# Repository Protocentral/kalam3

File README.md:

# ProtoCentral Kalam v3 IOT platform

ProtoCentral Kalam v3 is our newest IOT platform based on the ESP8266 Wi-Fi SoC. It's easy-to-use, low cost and easily scalable. 

IoT is now made easy with quick plug-and-play functionality in both hardware and software. Based on the popular ESP8266 Wi-Fi SoC from Espressif, this board contains everything required, right out of the box.

Features
--------
* ESP8266EX WiFi System-on-Chip (SoC) with ARM Cortex M3 microcontroller
* On-board 2.4 GHz PCB antenna
* FTDI-based USB-UART interface with microUSB connector
* Fully compatible with the Arduino IDE
* Single Li-Ion battery powered
* On-board battery charger
* 31-pin Hirose DF-9 connector on the back for expansion

Repository Contents
-------------------
* **/hardware** - All Eagle design files (.brd, .sch)
* **/libraries** - Arduino libraries and example code
* **/docs** - Additional Documentation

Board Overview
--------------

Kalam Starter Kit
---------
[Kalam Starter Kit Documentation](docs/starter_kit/README.md)

Getting Started with Kalam
--------------------------

Connect the GPIO expander cap to the Kalam V3 by stacking it on top.Now that the setup is complete,the setup needs to be powered up.Attach a Li-poly battery to the Kalam v2 Iot board.Control the power using the on/off switch

How to setup Arduino support for Kalam (using Sparkfun thing Dev)
---------------------------------------------------
Kalam is powered by the Sparkfun's board support file.The first thing you will need to do is to download the latest release of the Arduino IDE. You will need to be using version 1.6.4 or higher. 
After you have downloaded and installed v1.6.4, you will need to start the IDE and navigate to the Preferences menu.
Sparkfun's  JSON url for ESP8266 board is - https://raw.githubusercontent.com/sparkfun/Arduino_Boards/master/IDE_Board_Manager/package_sparkfun_index.json

* Click Ok to close and save the preferences
* Then click Tools > Board > Board Manager
* You should find Sparkfun ESP8266 boards listed in the Board Manager window.

*	Press the “Install” button on the chosen ESP8266 category.The download process will begin
* Reboot Arduino and look under Tools > Boards and you should see the addition of the Sparkfun boards in your board list.

Getting Started with ThingSpeak
-------------------------------
The Internet of Things (IoT) provides access to a broad range of embedded devices and web services. ThingSpeak is an IoT platform that enables you to collect, store, analyze, visualize, and act on data from sensors or actuators.The primary element of ThingSpeak activity is the channel, which contains data fields, location fields, and a status field. After you create a ThingSpeak channel, you can write data to the channel, process and view the data  and react to the data.

Setup ThingSpeak
----------------
ThingSpeak requires a user account and a channel. A channel is where you send data and where ThingSpeak stores data. Each channel has up to 8 data fields, location fields, and a status field. You can send data every 15 seconds to ThingSpeak.

* Sign up for new User Account – https://thingspeak.com/users/sign_up

* Create a new Channel by selecting Channels, My Channels, and then New Channel

You can change the name to fit your need and you can add a description corresponding to the channel. You can add any other useful description into the metadata field. In the same page, you should see the fields for Latitude, Longitude and Elevation. Also, you can make the channel as "Private" or "Public".

Once you have edited the fields, click on ‘Save Channel’ button.

Setup Arduino Sketch
--------------------

We have provided a few Arduino sketch examples . They are designed to work right away with no changes.  To make the examples work with your ThingSpeak channel, you will need to configure the myChannelNumber and myWriteAPIKey variables.

  ```
const char* tokenid = "OFZEOKCL95S8HRNI"

  ```
Running a sketch
-----------------------------------
Load the example in the Arduino IDE. Make sure to select the board as "Sparkfun ESP8266 Thing Dev"  and COM port. Then, upload the code to your Kalam.

License Information
-------------------
This product is open source!

Please use, reuse, and modify these files as you see fit. Please maintain attribution to Protocentral and release anything derivative under the same license.

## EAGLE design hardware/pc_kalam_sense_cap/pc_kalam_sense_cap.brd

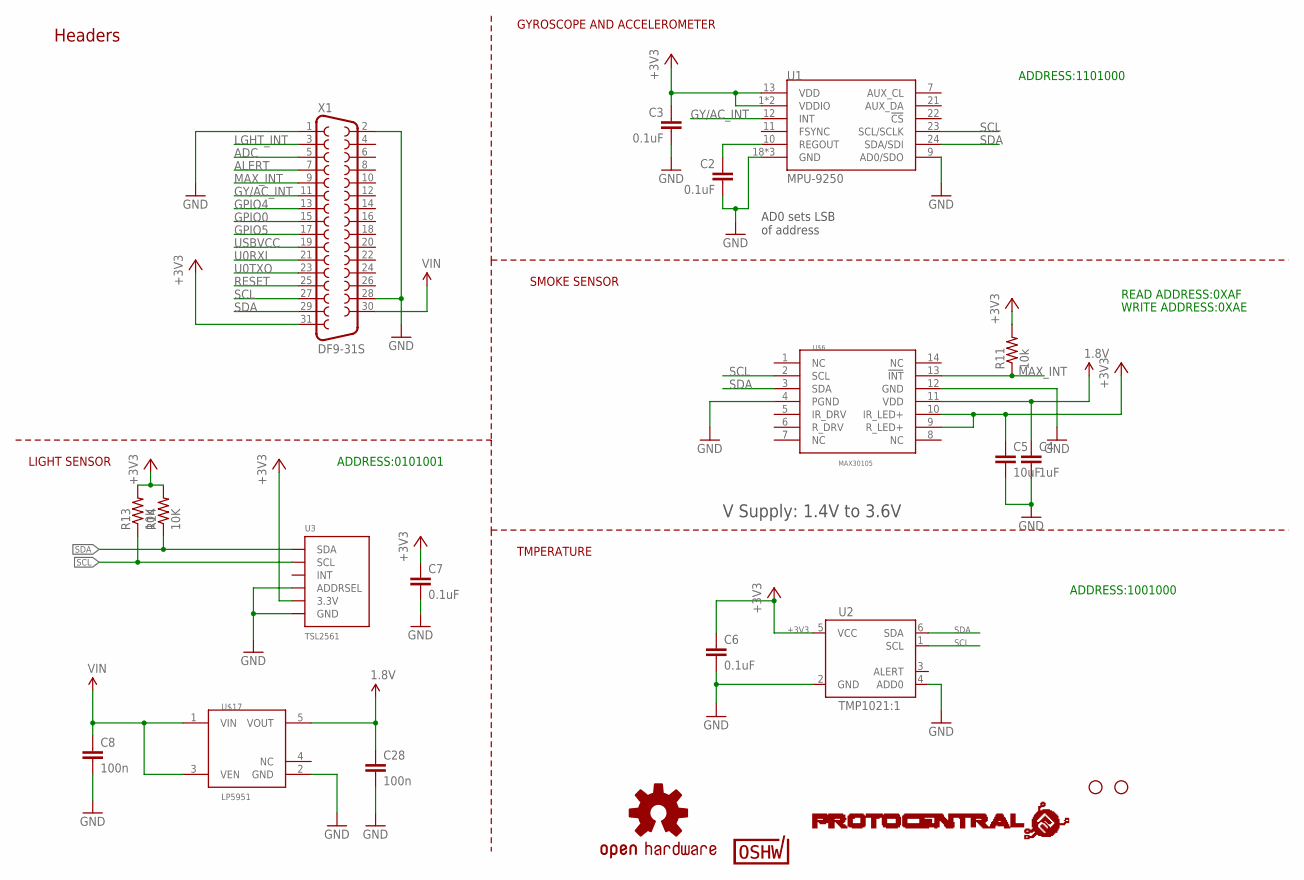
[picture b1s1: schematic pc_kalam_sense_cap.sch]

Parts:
C2, C3, C6: 0.1uF; 0603-CAP
C4: 1uF; C0805
C5: 10uF; C0805
C7: 0.1uF; C0805
C8, C28: 100n; C0402
R11: 10k; R0402
R13, R14: 10K; R0805
STANDOFF7, STANDOFF8: STAND-OFF
U1: MPU-9250; QFN24_PAD
U2: TMP1021:1; SOT563-2
U3: TSL2561; TSL2561_FN
U$2: CERT-SMALL; CERT-SMALL-SILK
U$3: OSHW-LOGOS; OSHW-LOGO-S
U$6: MAX30105; OESIP-14
U$9: PROTY_LOGO_WITH_TEXT; PROTY_WITH_TEXT
U$17: LP5951; SC70-5
X1: DF9-31S

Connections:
1.8V: C4.1, C28.1, U$6.11 (VDD), U$17.5 (VOUT)
+3V3: C3.1, C5.1, C6.1, C7.1, R11.2, R13.2, R14.2, U1.1 (VDDIO), U1.8 (VDDIO), U1.13 (VDD), U2.5 (VCC), U3.VDD (3.3V), U$6.9 (R_LED+), U$6.10 (IR_LED+), X1.31
ADC: X1.5
ALERT: X1.7
GND: C2.2, C3.2, C4.2, C5.2, C6.2, C7.2, C8.2, C28.2, U1.9 (AD0/SDO), U1.18 (GND), U1.20 (GND), U1.CENTER (GND), U2.2 (GND), U2.4 (ADD0), U3.ADR (ADDRSEL), U3.VSS (GND), U$6.4 (PGND), U$6.12 (GND), U$17.2 (GND), X1.1, X1.2, X1.28
GPIO0: X1.15
GPIO4: X1.13
GPIO5: X1.17
GY/AC_INT: U1.12 (INT), X1.11
LGHT_INT: X1.3
MAX_INT: R11.1, U$6.13 (!INT), X1.9
REGOUT: C2.1, U1.10 (REGOUT)
RESET: X1.25
SCL: R13.1, U1.23 (SCL/SCLK), U2.1 (SCL), U3.CLK (SCL), U$6.2 (SCL), X1.27
SDA: R14.1, U1.24 (SDA/SDI), U2.6 (SDA), U3.DATA (SDA), U$6.3 (SDA), X1.29
U0RXI: X1.21
U0TXO: X1.23
USBVCC: X1.19
VIN: C8.1, U$17.1 (VIN), U$17.3 (VEN), X1.30

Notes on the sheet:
Headers
AD0 sets LSB of address
V Supply: 1.4V to 3.6V
TMPERATURE
SMOKE SENSOR
GYROSCOPE AND ACCELEROMETER
LIGHT SENSOR
ADDRESS:1101000
ADDRESS:1001000
ADDRESS:0101001
READ ADDRESS:0XAF
WRITE ADDRESS:0XAE

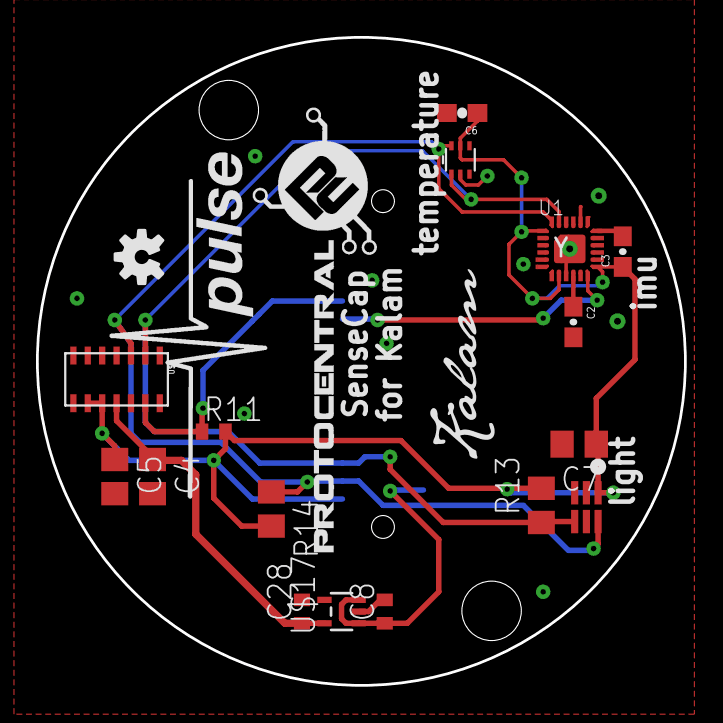
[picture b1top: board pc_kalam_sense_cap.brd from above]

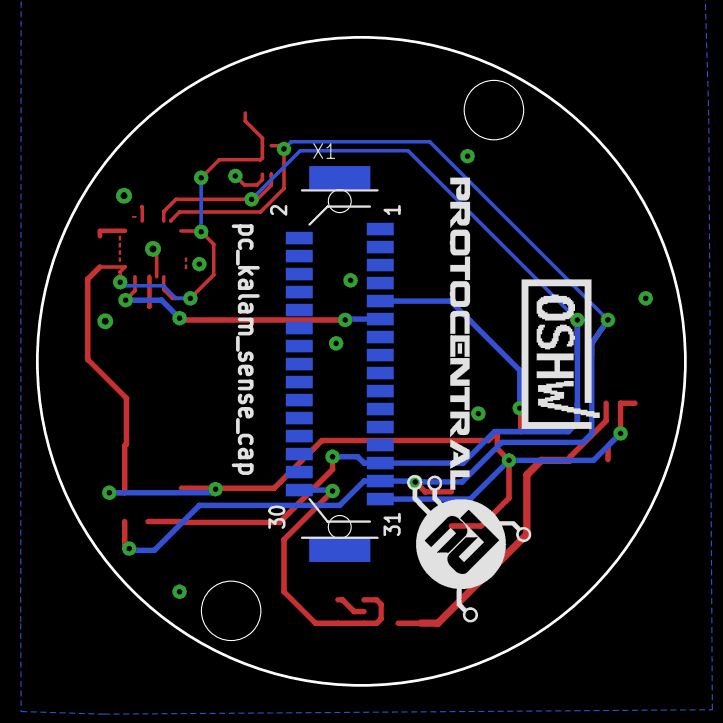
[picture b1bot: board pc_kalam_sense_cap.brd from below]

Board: 4 copper layers, 36.0 x 36.0 mm, 25 parts (5 on the bottom side), 9 nets.

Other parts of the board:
U$1: PULSE
U$4: KALAM-NAME-ONLY
U$5: PROTY_LOGO_WITH_TEXT; PROTY_WITH_TEXT

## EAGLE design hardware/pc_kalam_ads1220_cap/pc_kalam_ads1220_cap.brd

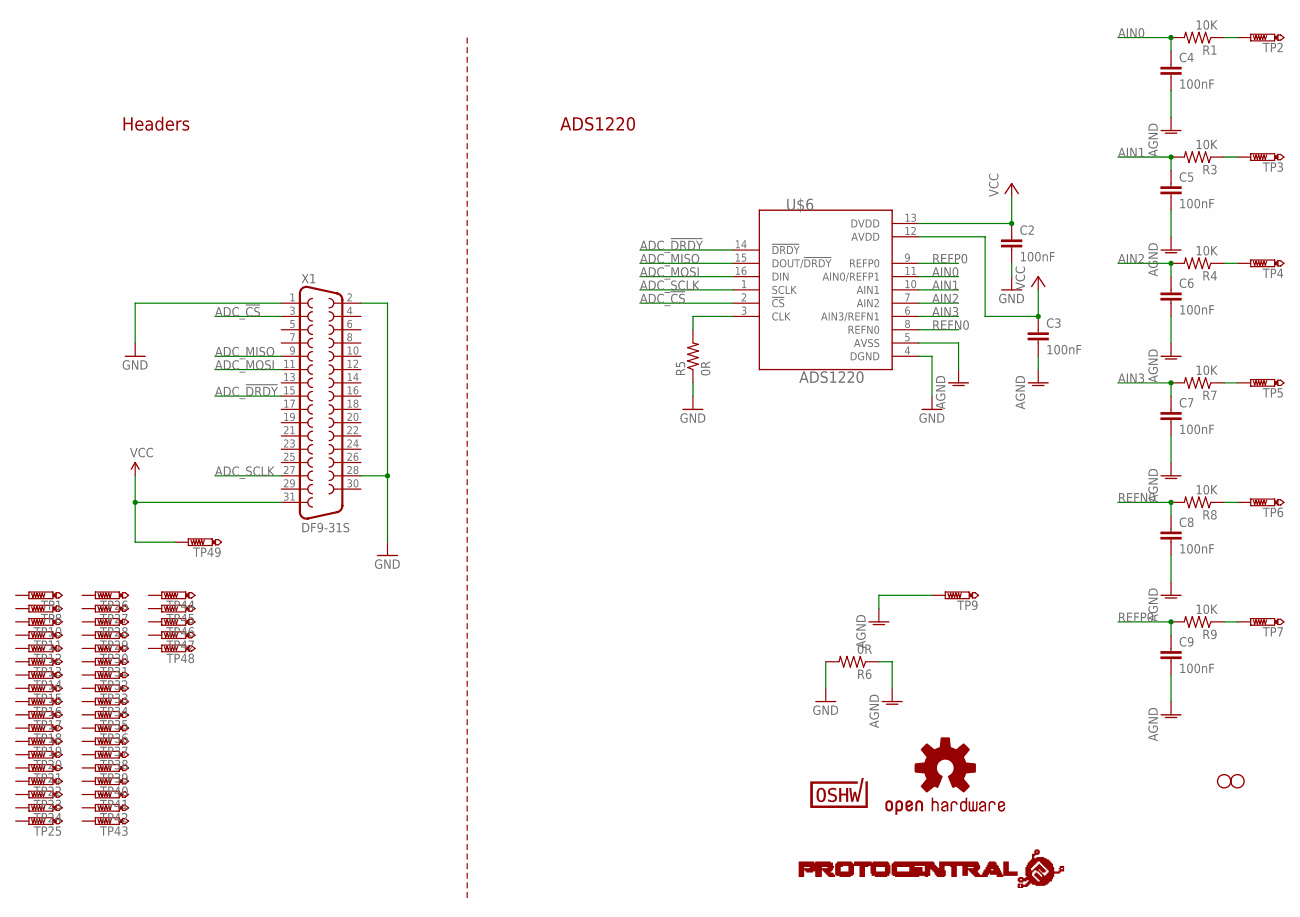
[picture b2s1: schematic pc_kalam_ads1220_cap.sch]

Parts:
C2, C3, C4, C5, C6, C7, C8, C9: 100nF; C0805
R1, R3, R4, R7, R8, R9: 10K; R0805
R5, R6: 0R; R0805
STANDOFF7, STANDOFF8: STAND-OFF
TP1, TP2, TP3, TP4, TP5, TP6, TP7, TP8, TP9, TP10, TP11, TP12, TP13, TP14, TP15, TP16, TP17, TP18, TP19, TP20, TP21, TP22, TP23, TP24, TP25, TP26, TP27, TP28, TP29, TP30, TP31, TP32, TP33, TP34, TP35, TP36, TP37, TP38, TP39, TP40, TP41, TP42, TP43, TP44, TP45, TP46, TP47, TP48, TP49: PTR1PAD1-13; P1-13
U$1: PROTY-LOGO; LOGO-PROTY
U$2: CERT-SMALL; CERT-SMALL-SILK
U$3: OSHW-LOGOS; OSHW-LOGO-S
U$6: ADS1220; TSSOP-16
X1: DF9-31S

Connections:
ADC_!CS: U$6.2 (!CS), X1.3
ADC_!DRDY: U$6.14 (!DRDY), X1.15
ADC_CLK: R5.2, U$6.3 (CLK)
ADC_MISO: U$6.15 (DOUT/!DRDY), X1.9
ADC_MOSI: U$6.16 (DIN), X1.11
ADC_SCLK: U$6.1 (SCLK), X1.27
AGND: C3.2, C4.2, C5.2, C6.2, C7.2, C8.2, C9.2, R6.1, TP9.TP, U$6.5 (AVSS)
AIN0: C4.1, R1.2, U$6.11 (AIN0/REFP1)
AIN1: C5.1, R3.2, U$6.10 (AIN1)
AIN2: C6.1, R4.2, U$6.7 (AIN2)
AIN3: C7.1, R7.2, U$6.6 (AIN3/REFN1)
GND: C2.2, R5.1, R6.2, U$6.4 (DGND), X1.1, X1.2, X1.28
unnamed: R1.1, TP2.TP
unnamed: R3.1, TP3.TP
unnamed: R4.1, TP4.TP
unnamed: R7.1, TP5.TP
unnamed: R8.1, TP6.TP
unnamed: R9.1, TP7.TP
REFN0: C8.1, R8.2, U$6.8 (REFN0)
REFP0: C9.1, R9.2, U$6.9 (REFP0)
VCC: C2.1, C3.1, TP49.TP, U$6.12 (AVDD), U$6.13 (DVDD), X1.31

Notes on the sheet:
Headers
ADS1220

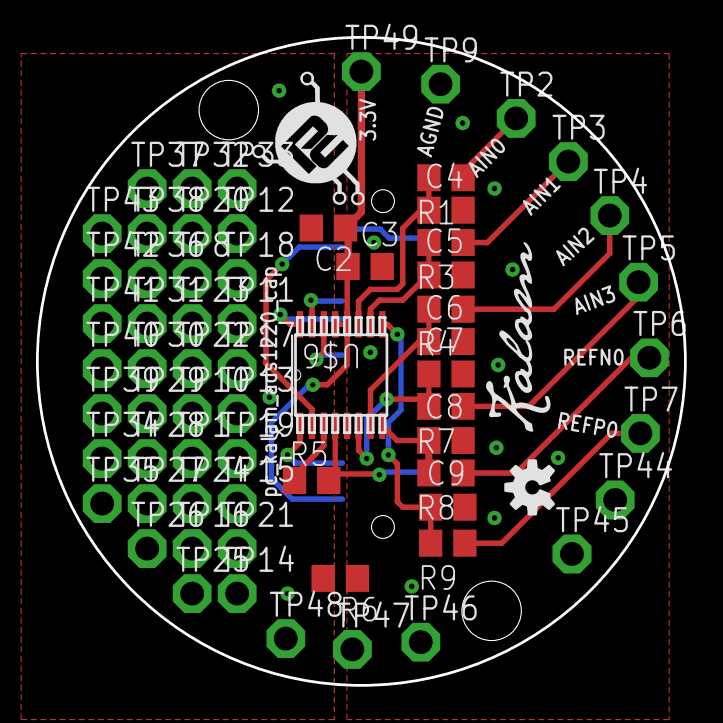
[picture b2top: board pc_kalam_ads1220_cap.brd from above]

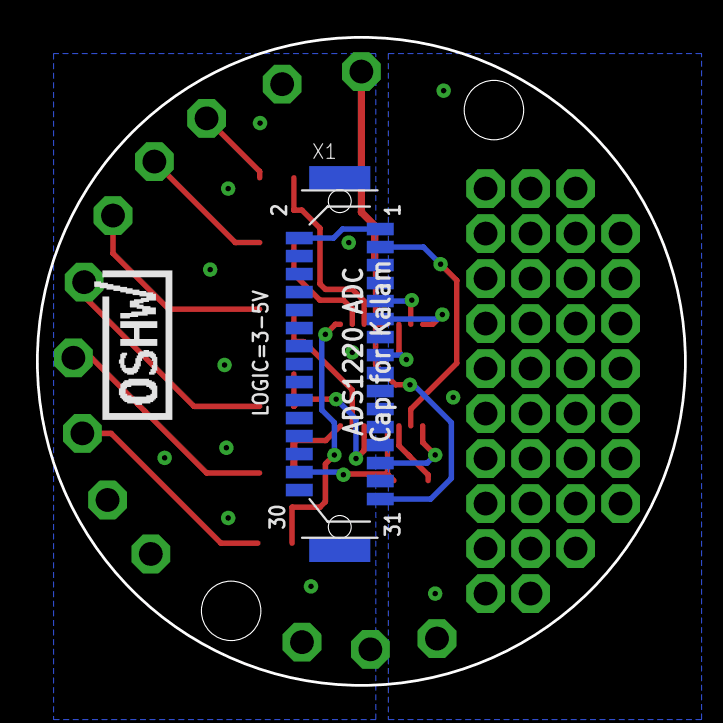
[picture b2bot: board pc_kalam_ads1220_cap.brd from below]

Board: 4 copper layers, 36.0 x 36.0 mm, 73 parts (4 on the bottom side), 21 nets.

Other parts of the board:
U$4: KALAM-NAME-ONLY

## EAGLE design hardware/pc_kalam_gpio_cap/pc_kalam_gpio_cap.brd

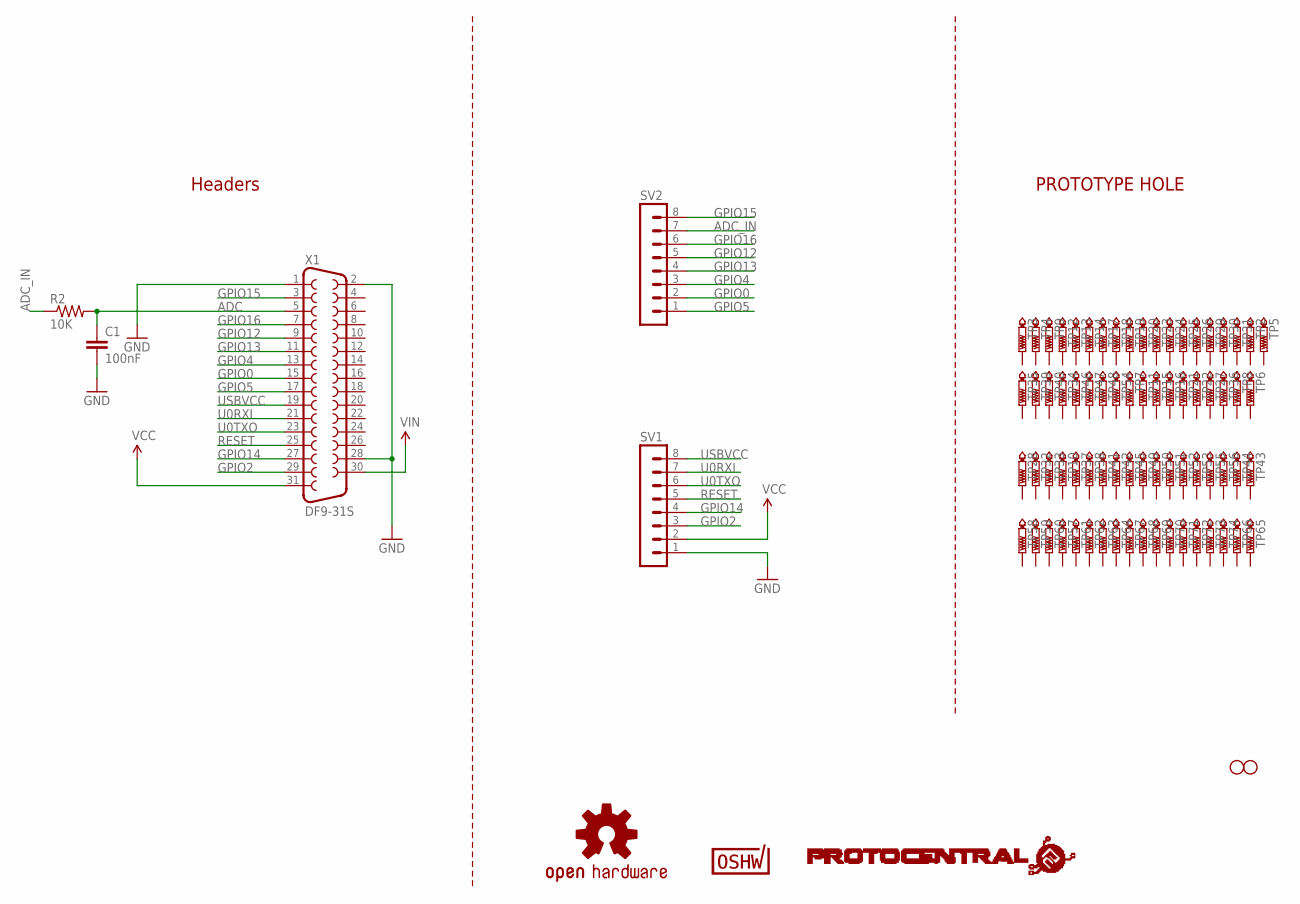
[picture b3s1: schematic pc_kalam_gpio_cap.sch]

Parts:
C1: 100nF; C0805
R2: 10K; R0805
STANDOFF7, STANDOFF8: STAND-OFF
SV1, SV2: MA08-1
TP2, TP3, TP4, TP5, TP6, TP7, TP8, TP9, TP10, TP11, TP12, TP13, TP14, TP15, TP16, TP17, TP18, TP19, TP20, TP21, TP22, TP23, TP24, TP25, TP26, TP27, TP28, TP29, TP30, TP31, TP32, TP33, TP34, TP35, TP36, TP37, TP38, TP39, TP40, TP41, TP42, TP43, TP44, TP45, TP46, TP47, TP48, TP49, TP50, TP51, TP52, TP53, TP54, TP55, TP56, TP57, TP58, TP59, TP60, TP61, TP62, TP63, TP64, TP65, TP66, TP67, TP68, TP69, TP70, TP71, TP72, TP73, TP74: PTR1PAD1-13; P1-13
U$2: CERT-SMALL; CERT-SMALL-SILK
U$3: OSHW-LOGOS; OSHW-LOGO-S
U$6: PROTY_LOGO_WITH_TEXT; PROTY_WITH_TEXT
X1: DF9-31S

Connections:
ADC: C1.1, R2.2, X1.5
ADC_IN: R2.1, SV2.7
GND: C1.2, SV1.1, X1.1, X1.2, X1.28
GPIO0: SV2.2, X1.15
GPIO2: SV1.3, X1.29
GPIO4: SV2.3, X1.13
GPIO5: SV2.1, X1.17
GPIO12: SV2.5, X1.9
GPIO13: SV2.4, X1.11
GPIO14: SV1.4, X1.27
GPIO15: SV2.8, X1.3
GPIO16: SV2.6, X1.7
RESET: SV1.5, X1.25
U0RXI: SV1.7, X1.21
U0TXO: SV1.6, X1.23
USBVCC: SV1.8, X1.19
VCC: SV1.2, X1.31
VIN: X1.30

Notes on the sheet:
Headers
PROTOTYPE HOLE

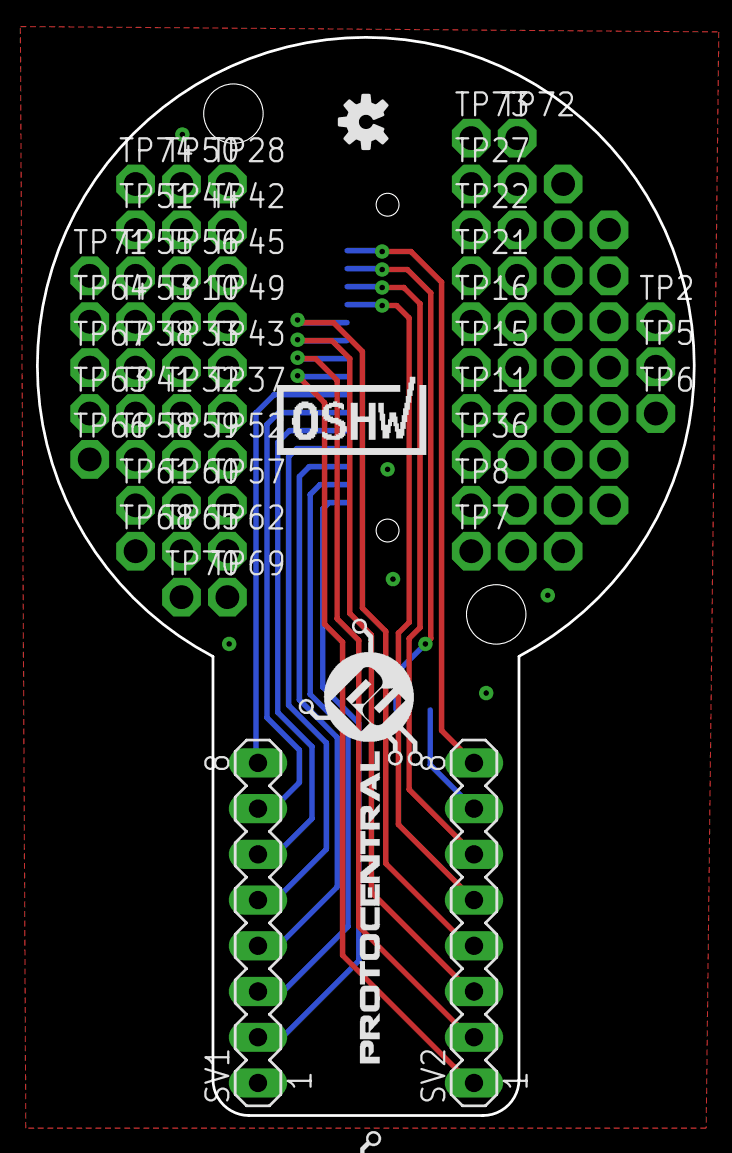
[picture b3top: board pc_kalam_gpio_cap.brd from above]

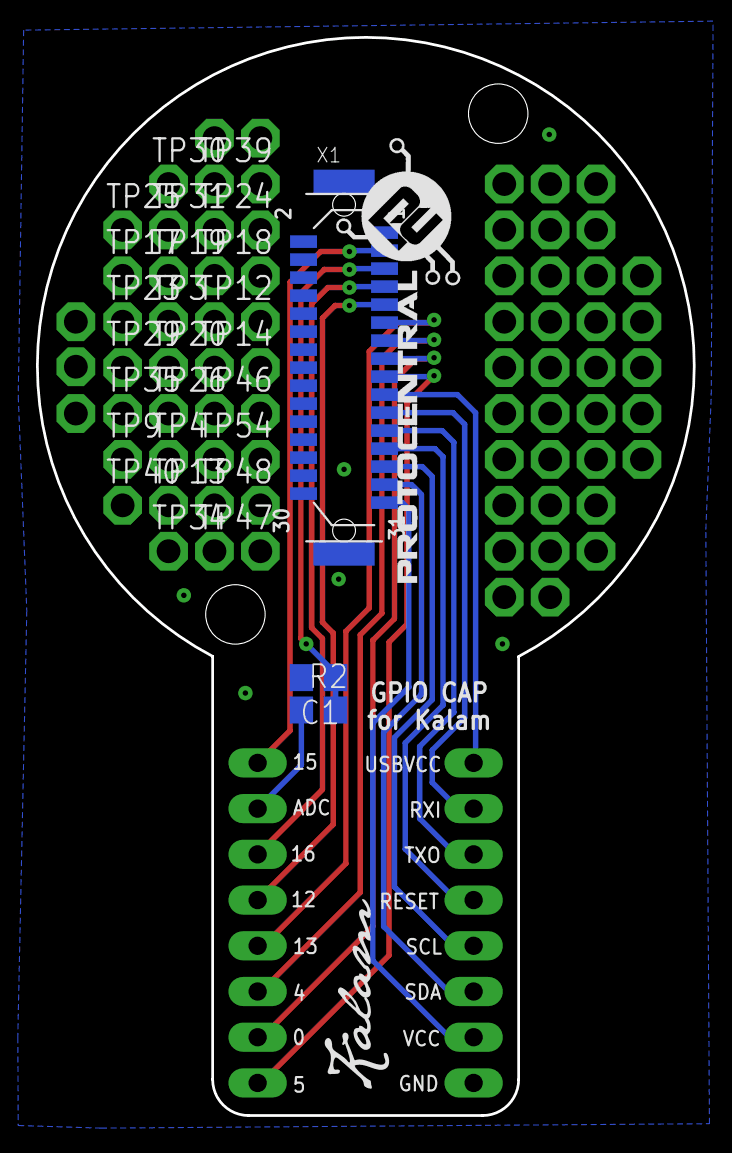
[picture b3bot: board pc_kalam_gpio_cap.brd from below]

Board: 4 copper layers, 36.5 x 59.9 mm, 86 parts (32 on the bottom side), 17 nets.

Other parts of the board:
U$1, U$5: PROTY_LOGO_WITH_TEXT; PROTY_WITH_TEXT
U$4: KALAM-NAME-ONLY

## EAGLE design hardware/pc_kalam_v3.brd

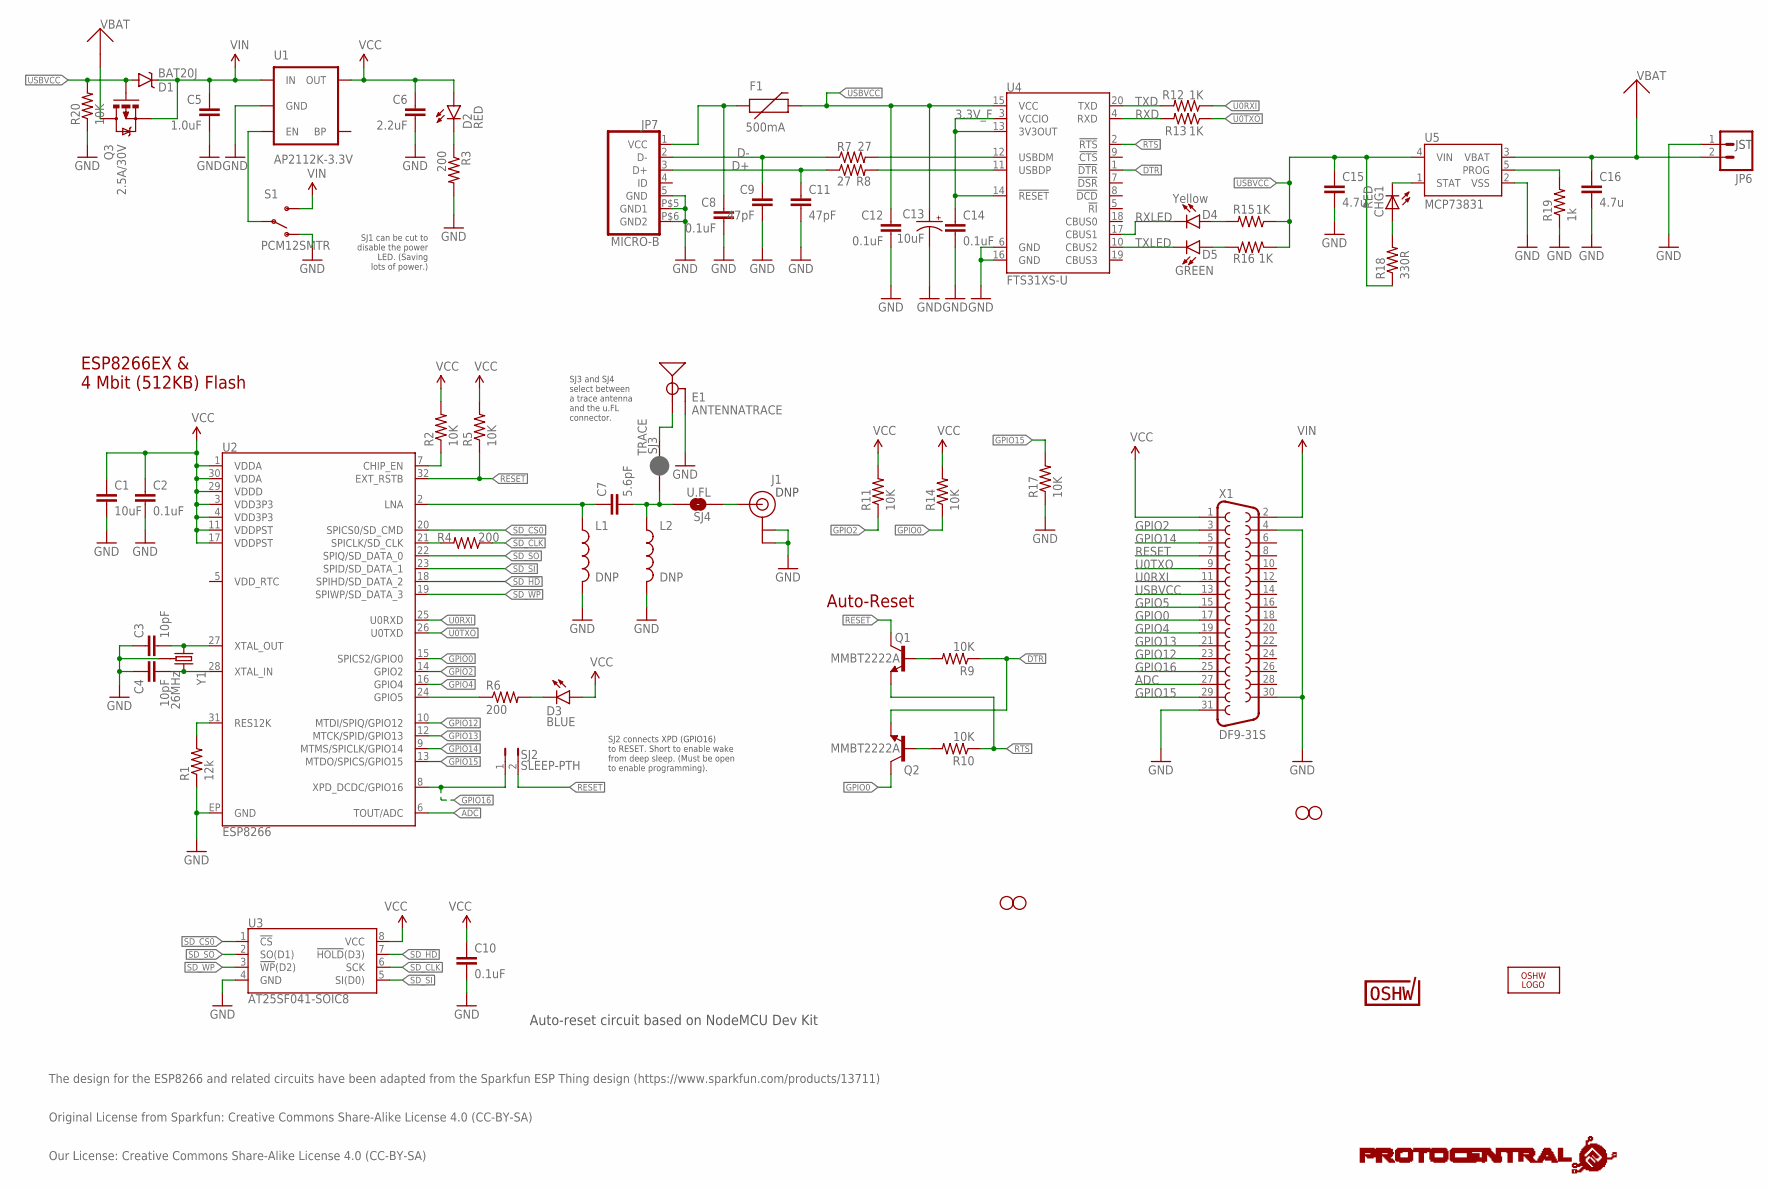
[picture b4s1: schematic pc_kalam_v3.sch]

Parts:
C1: 10uF; 0603-CAP
C2, C10, C12, C14: 0.1uF; 0603-CAP
C3, C4: 10pF; 0603-CAP
C5: 1.0uF; 0805
C6: 2.2uF; 0603-CAP
C7: 5.6pF; 0603-CAP
C8: 0.1uF; C0402
C9, C11: 47pF; 0603-CAP
C13: 10uF; EIA3216
C15, C16: 4.7u; C0805
CHG1: RED; CHIPLED_0603
D1: BAT20J; SOD-323
D2: RED; LED-0603
D3: BLUE; LED-0603
D4: Yellow; LED-0603
D5: GREEN; LED-0603
E1: ANTENNATRACE; TRACE_ANTENNA_2.4GHZ_25.7MM
F1: 500mA; PTC-1206
J1: DNP; U.FL
JP6: M02-JST-2MM-SMT; JST-2-SMD
JP7: MICRO-B
L1, L2: DNP; 0603
LOGO2: OSHW_LOGO_FILLX0200-NT; OSHW_FILLX200_NOTEXT
Q1, Q2: MMBT2222A; SOT23-3@1
Q3: 2.5A/30V; SOT23-3
R1: 12k; 0603-RES
R2, R5, R9, R10, R11, R14, R17: 10K; 0603-RES
R3, R4, R6: 200; 0603-RES
R7, R8: 27; 0603-RES
R12, R13, R15, R16: 1K; 0603-RES
R18: 330R; R0402
R19: 1k; R0402
R20: 10K; R0402
S1: PCM12SMTR; SWITCH-SPST-SMD-A
SJ2: SLEEP-PTH; PTH-JUMPER-2-NO_NO_SILK
SJ3: TRACE; PAD-JUMPER-2-NC_BY_PASTE_NO_SILK
SJ4: U.FL; PAD-JUMPER-2-NO_NO_SILK
STANDOFF1, STANDOFF2, STANDOFF3, STANDOFF4: STAND-OFF
U1: AP2112K-3.3V; SOT23-5
U2: ESP8266; QFN32
U3: AT25SF041-SOIC8; SO08
U4: FTS31XS-U; SSOP20_L
U5: MCP73831; SOT23-5
U$1: PROTY_LOGO_WITH_TEXT; PROTY_WITH_TEXT
U$5: CERT-MEDIUM; CERT-MED-SILK
U$8: PROTY-LOGO; LOGO-PROTY
X1: DF9-31S
Y1: 26MHz; CRYSTAL-SMD-3.2X2.5

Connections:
3.3V_F: C14.1, U4.3 (VCCIO), U4.13 (3V3OUT), U4.14 (!RESET)
ADC: U2.6 (TOUT/ADC), X1.27
ANT: J1.P$3 (SIGNAL), SJ4.1
CHIP_EN: R2.1, U2.7 (CHIP_EN)
D+: C11.1, JP7.3 (D+), R8.1
D-: C9.1, JP7.2 (D-), R7.1
DTR: Q2.2 (E), R9.1, U4.1 (!DTR)
GND: C1.2, C2.2, C3.1, C4.1, C5.2, C6.2, C8.2, C9.2, C10.2, C11.2, C12.2, C13.C (-), C14.2, C15.2, C16.2, E1.GND, E1.GND2 (GND), J1.P$1 (GND), J1.P$2 (GND), JP6.1, JP7.5 (GND), JP7.P$5 (GND1), JP7.P$6 (GND2), L1.2, L2.2, R1.1, R3.2, R17.1, R19.1, R20.1, S1.1 (O), U1.2 (GND), U2.EP (GND), U3.4 (GND), U4.6 (GND), U4.16 (GND), U5.2 (VSS), X1.4, X1.30, X1.31, Y1.2 (GND), Y1.4 (GND)
GPIO0: Q2.3 (C), R14.1, U2.15 (SPICS2/GPIO0), X1.17
GPIO2: R11.1, U2.14 (GPIO2), X1.3
GPIO4: U2.16 (GPIO4), X1.19
GPIO5: R6.1, U2.24 (GPIO5), X1.15
GPIO12: U2.10 (MTDI/SPIQ/GPIO12), X1.23
GPIO13: U2.12 (MTCK/SPID/GPIO13), X1.21
GPIO14: U2.9 (MTMS/SPICLK/GPIO14), X1.5
GPIO15: R17.2, U2.13 (MTDO/SPICS/GPIO15), X1.29
GPIO16: SJ2.1, U2.8 (XPD_DCDC/GPIO16), X1.25
LNA: C7.1, L1.1, U2.2 (LNA)
LNA2: C7.2, L2.1, SJ3.1, SJ4.2
unnamed: R1.2, U2.31 (RES12K)
unnamed: C4.2, U2.28 (XTAL_IN), Y1.3 (2)
unnamed: C3.2, U2.27 (XTAL_OUT), Y1.1
unnamed: R7.2, U4.12 (USBDM)
unnamed: Q1.1 (B), R9.2
unnamed: R8.2, U4.11 (USBDP)
unnamed: D5.A, R16.2
unnamed: D3.C, R6.2
unnamed: D4.A, R15.2
unnamed: D2.C, R3.1
unnamed: Q2.1 (B), R10.2
unnamed: CHG1.C, U5.1 (STAT)
unnamed: S1.2, U1.3 (EN)
unnamed: CHG1.A, R18.2
unnamed: R19.2, U5.5 (PROG)
RESET: Q1.3 (C), R5.1, SJ2.2, U2.32 (EXT_RSTB), X1.7
RTS: Q1.2 (E), R10.1, U4.2 (!RTS)
RXD: R13.2, U4.4 (RXD)
RXLED: D4.C, U4.17 (CBUS1)
SD_!HD!: U2.18 (SPIHD/SD_DATA_2), U3.7 (!HOLD!(D3))
SD_!WP!: U2.19 (SPIWP/SD_DATA_3), U3.3 (!WP!(D2))
SD_CLK: R4.1, U3.6 (SCK)
SD_CLK0: R4.2, U2.21 (SPICLK/SD_CLK)
SD_CS0: U2.20 (SPICS0/SD_CMD), U3.1 (!CS!)
SD_SI: U2.23 (SPID/SD_DATA_1), U3.5 (SI(D0))
SD_SO: U2.22 (SPIQ/SD_DATA_0), U3.2 (SO(D1))
TRACE_ANT: E1.ANT (SIGNAL), SJ3.2
TXD: R12.2, U4.20 (TXD)
TXLED: D5.C, U4.10 (CBUS2)
U0RXI: R12.1, U2.25 (U0RXD), X1.11
U0TXO: R13.1, U2.26 (U0TXD), X1.9
USBVCC: C12.1, C13.A (+), C15.1, D1.A, F1.2, Q3.1 (G), R15.1, R16.1, R18.1, R20.2, U4.15 (VCC), U5.4 (VIN), X1.13
VBAT: C16.1, JP6.2, Q3.3 (D), U5.3 (VBAT)
VCC: C1.1, C2.1, C6.1, C10.1, D2.A, D3.A, R2.2, R5.2, R11.2, R14.2, U1.5 (OUT), U2.1 (VDDA), U2.3 (VDD3P3), U2.4 (VDD3P3), U2.11 (VDDPST), U2.17 (VDDPST), U2.29 (VDDD), U2.30 (VDDA), U3.8 (VCC), X1.1
VIN: C5.1, D1.C, Q3.2 (S), S1.3 (S), U1.1 (IN), X1.2
VUSB: C8.1, F1.1, JP7.1 (VCC)

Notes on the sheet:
ESP8266EX & 4 Mbit (512KB) Flash
Auto-Reset
JST
SJ2 connects XPD (GPIO16) to RESET. Short to enable wake from deep sleep. (Must be open to enable programming).
SJ1 can be cut to disable the power LED. (Saving lots of power.)
DNP
Auto-reset circuit based on NodeMCU Dev Kit
SJ3 and SJ4 select between a trace antenna and the u.FL connector.
The design for the ESP8266 and related circuits have been adapted from the Sparkfun ESP Thing design (https://www.sparkfun.com/products/13711)
Original License from Sparkfun: Creative Commons Share-Alike License 4.0 (CC-BY-SA)
Our License: Creative Commons Share-Alike License 4.0 (CC-BY-SA)

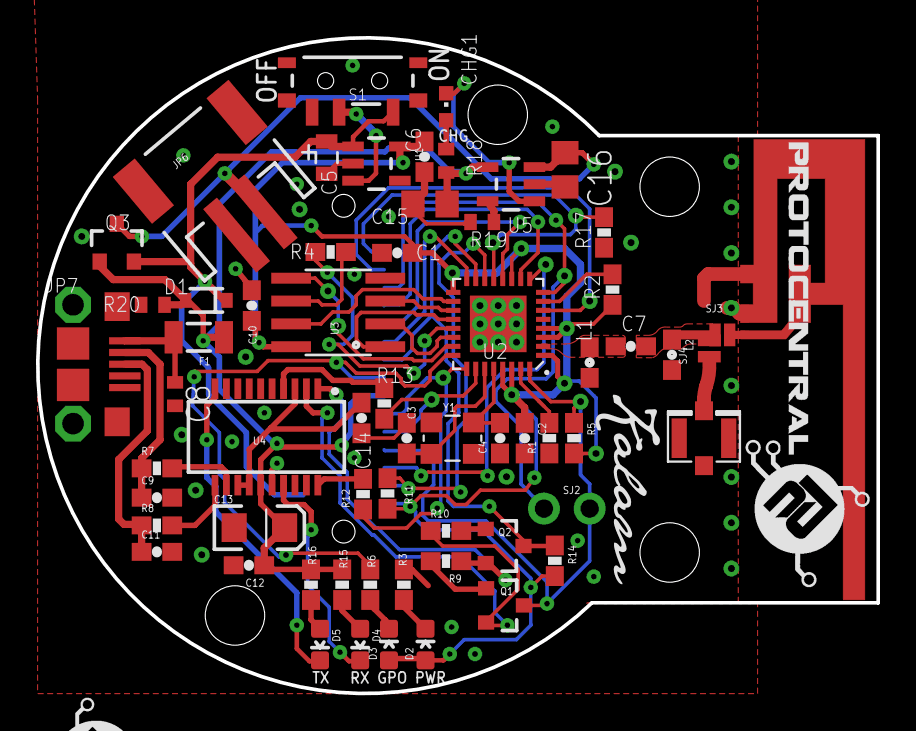
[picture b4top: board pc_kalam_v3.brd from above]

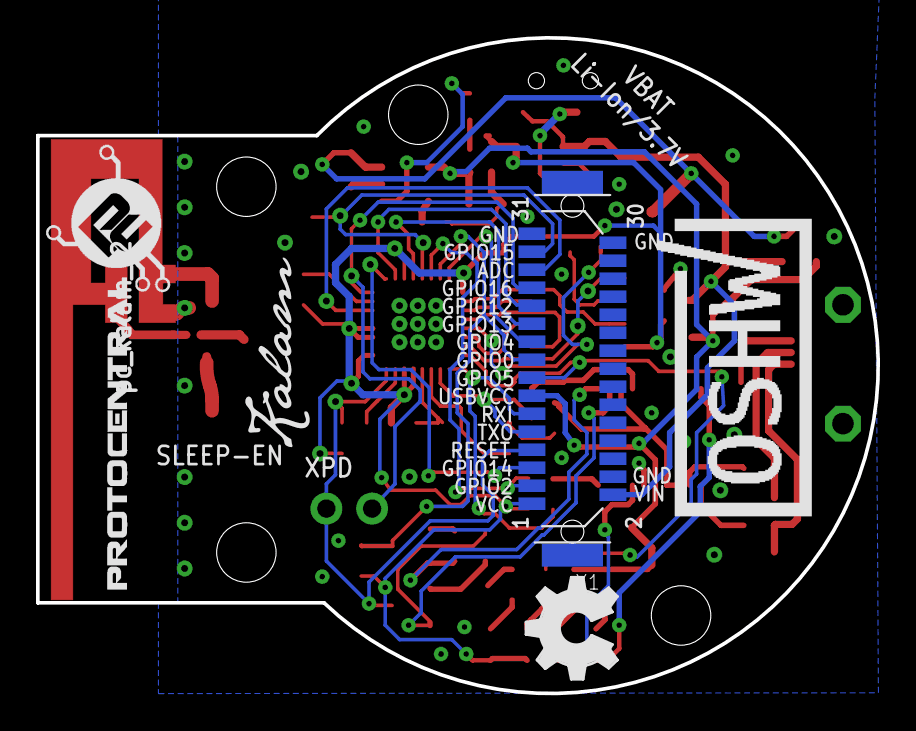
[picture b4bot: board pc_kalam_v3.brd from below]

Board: 4 copper layers, 46.7 x 36.4 mm, 74 parts (5 on the bottom side), 55 nets.

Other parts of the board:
U$2: PROTY_LOGO_WITH_TEXT; PROTY_WITH_TEXT
U$3, U$4: KALAM-NAME-ONLY

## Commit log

2017-02-06 Updated Images
2017-02-07 added images
2017-02-07 added image
2017-02-12 Added design files for GPIO cap
2017-02-12 Uploaded all cap designs
2017-02-13 Added interactive wreath example
2017-03-15 Added gitignore
2017-03-15 Added Starter Kit documentation
2017-03-15 Set theme jekyll-theme-modernist
2017-03-15 Updated Starter Kit documentation
2017-03-15 Added README to docs
2017-03-15 Set theme jekyll-theme-tactile
2017-03-15 upadated the image
2017-03-21 Added Hello Thingspeak example

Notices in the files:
parts and their libraries:
SparkFun-Electromechanical: Licensing: Creative Commons ShareAlike 4.0 International - https://creativecommons.org/licenses/by-sa/4.0
SparkFun: Licensing: CC v3.0 Share-Alike You are welcome to use this library for commercial purposes.
